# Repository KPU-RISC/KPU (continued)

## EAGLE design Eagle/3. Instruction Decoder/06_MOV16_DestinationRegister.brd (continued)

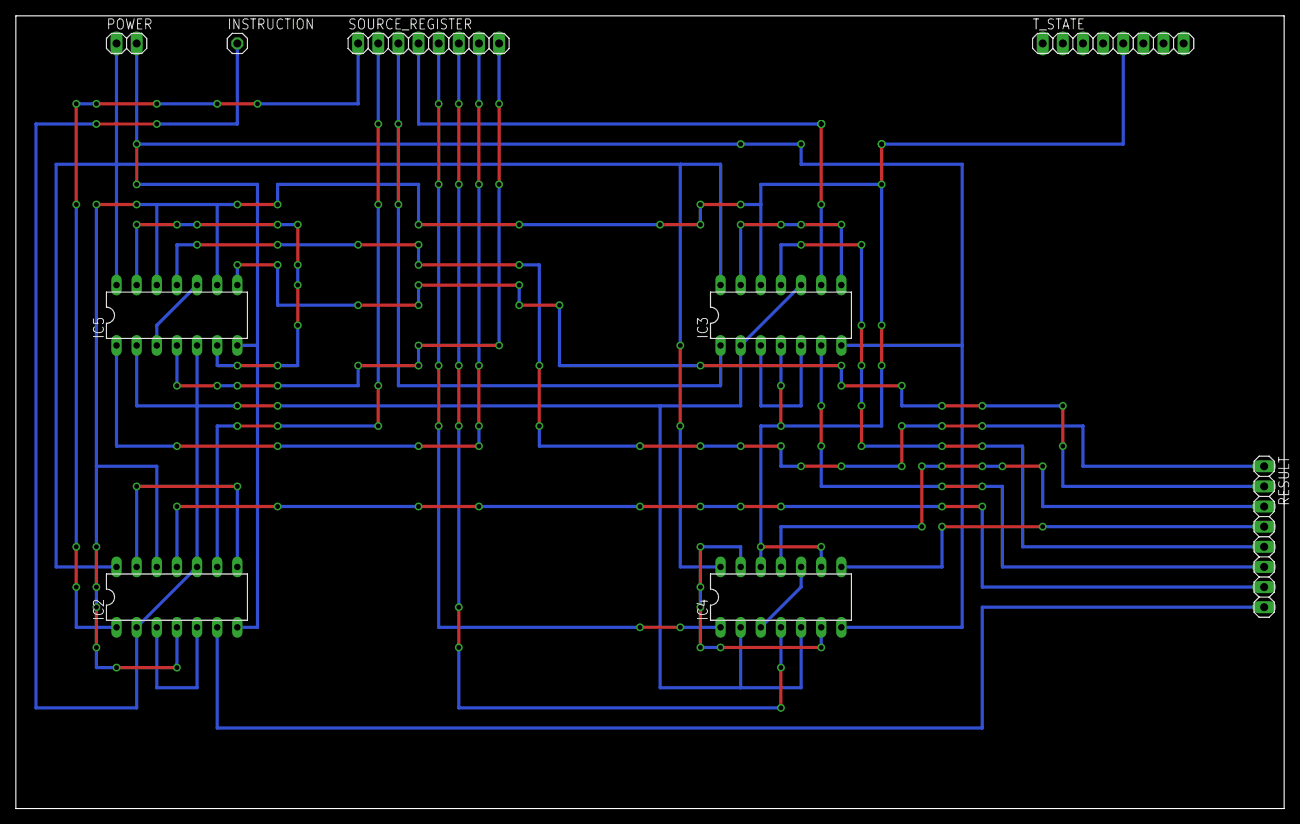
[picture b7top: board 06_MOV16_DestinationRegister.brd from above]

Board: 2 copper layers, 160.0 x 100.0 mm, 9 parts (0 on the bottom side), 28 nets.

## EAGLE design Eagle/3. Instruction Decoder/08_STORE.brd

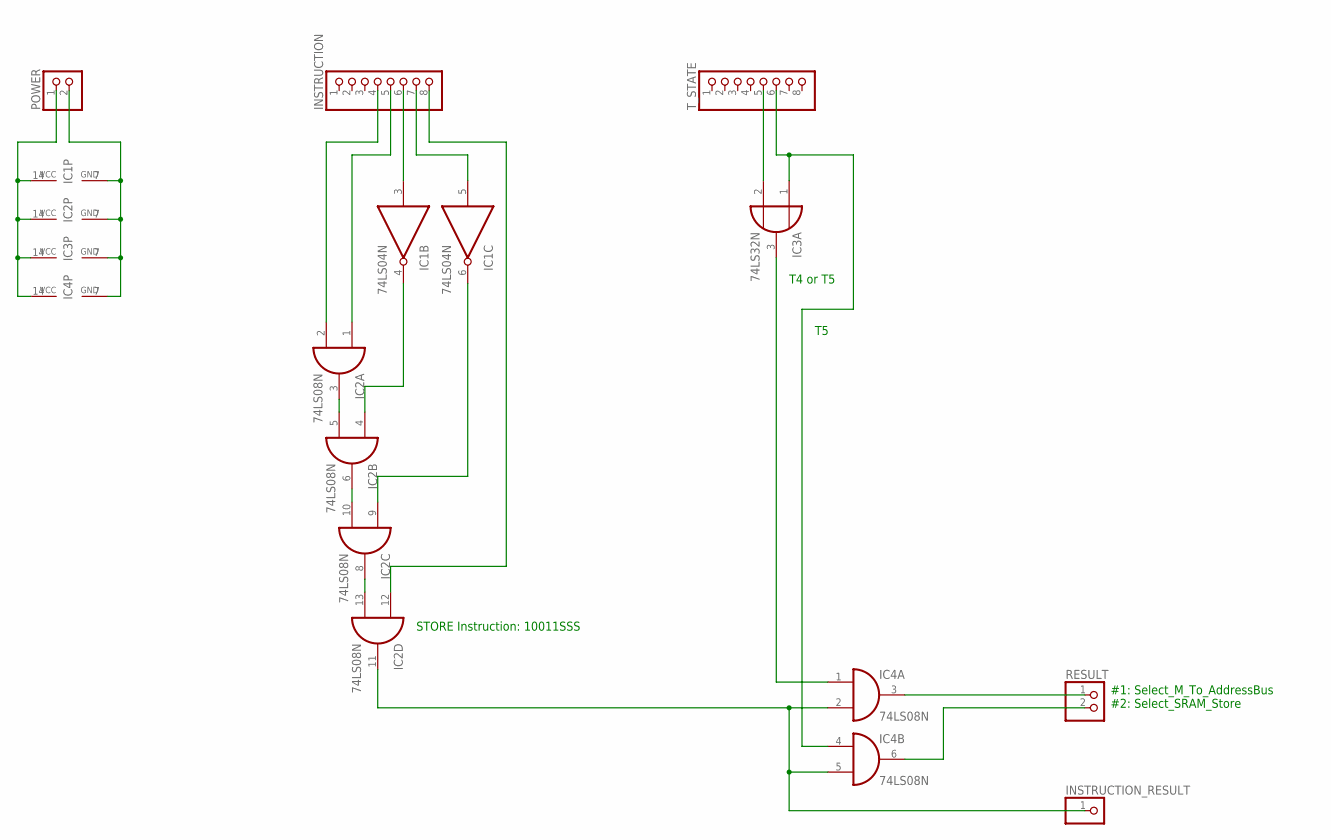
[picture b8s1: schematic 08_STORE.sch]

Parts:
IC1: 74LS04N; DIL14
IC2, IC4: 74LS08N; DIL14
IC3: 74LS32N; DIL14
INSTRUCTION: PINHD-1X8; 1X08
INSTRUCTION_RESULT: PINHD-1X1; 1X01
POWER: PINHD-1X2; 1X02
RESULT: PINHD-1X2; 1X02
T_STATE: PINHD-1X8; 1X08

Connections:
GND: IC1.7 (GND), IC2.7 (GND), IC3.7 (GND), IC4.7 (GND), POWER.2
unnamed: IC2.2 (I1), INSTRUCTION.4
unnamed: IC1.3 (I), INSTRUCTION.6
unnamed: IC1.5 (I), INSTRUCTION.7
unnamed: IC2.1 (I0), INSTRUCTION.5
unnamed: IC2.3 (O), IC2.5 (I1)
unnamed: IC1.4 (O), IC2.4 (I0)
unnamed: IC2.6 (O), IC2.10 (I1)
unnamed: IC1.6 (O), IC2.9 (I0)
unnamed: IC2.8 (O), IC2.13 (I1)
unnamed: IC2.12 (I0), INSTRUCTION.8
unnamed: IC3.2 (I1), T_STATE.5
unnamed: IC3.1 (I0), IC4.4 (I0), T_STATE.6
unnamed: IC2.11 (O), IC4.2 (I1), IC4.5 (I1), INSTRUCTION_RESULT.1
unnamed: IC3.3 (O), IC4.1 (I0)
unnamed: IC4.6 (O), RESULT.2
RESULT: IC4.3 (O), RESULT.1
VCC: IC1.14 (VCC), IC2.14 (VCC), IC3.14 (VCC), IC4.14 (VCC), POWER.1

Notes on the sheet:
STORE Instruction: 10011SSS
T4 or T5
#1: Select_M_To_AddressBus #2: Select_SRAM_Store

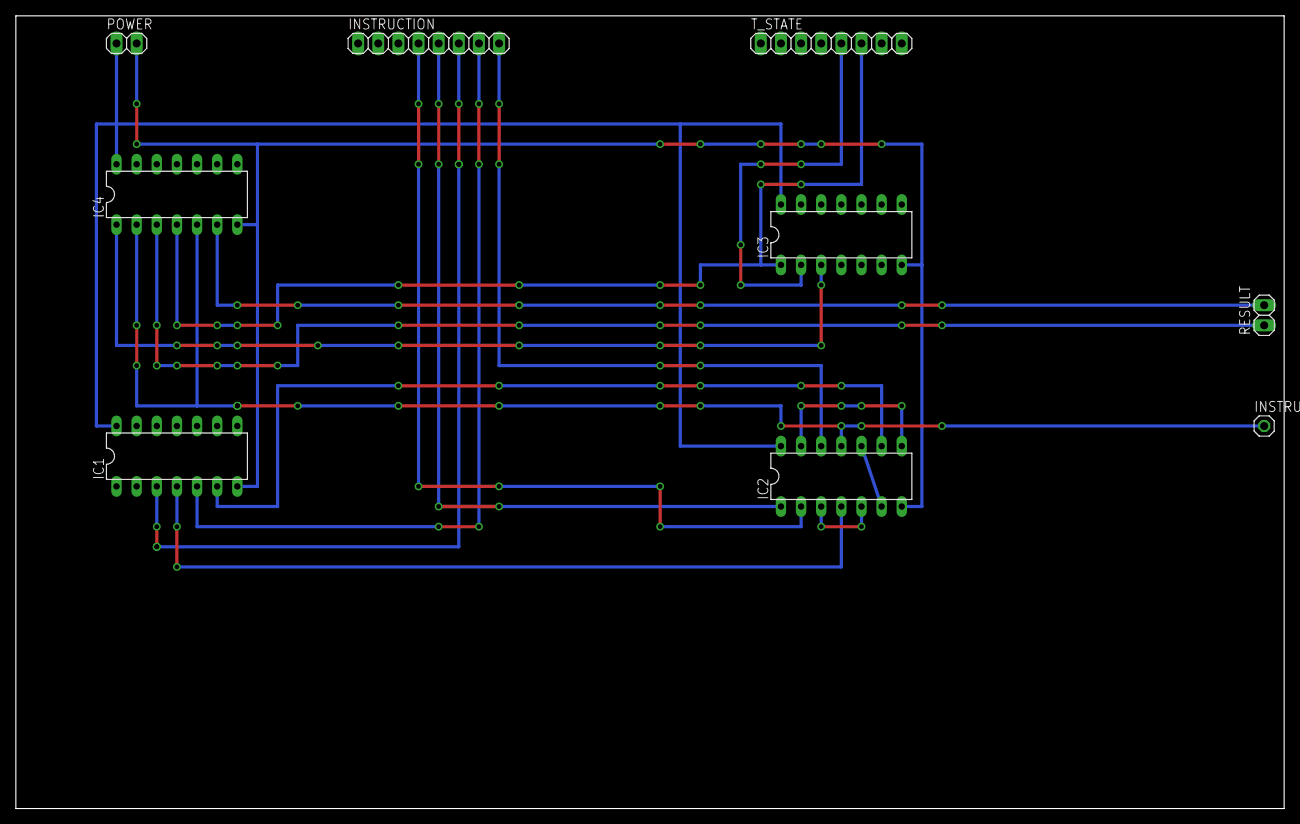
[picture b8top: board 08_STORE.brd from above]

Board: 2 copper layers, 160.0 x 100.0 mm, 9 parts (0 on the bottom side), 18 nets.

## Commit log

2016-12-14 Update LICENSE
2017-04-16 Initial code base
2017-04-16 Included ANTLR 4.5 References
2017-04-16 Added Assembly Code
2017-04-16 VHDL Description of the various CPU components
2017-04-16 Added Emulation files
2017-04-16 Added Eagle files
2017-04-16 Added Logicly files
2017-04-16 Fixed hard coded paths.
2017-04-16 Moved.
2017-04-16 Changed hardcoded file paths.
2017-04-16 Assembly example for INT usage.
2017-04-16 Added INT implementation.
2017-04-16 Fixed the INT implementation.
2017-04-16 Fixed some problems for accessing the disk.
2017-10-26 New Layout for SHL ALU operation
2017-11-04 Added new schematics.
